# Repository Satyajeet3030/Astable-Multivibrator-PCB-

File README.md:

# Astable Multivibrator PCB Design

Overview
This project is a PCB design of an Astable Multivibrator created using KiCad.

 Features
- Two-transistor astable multivibrator
- Through-hole components
- Single-layer PCB
- Compact board layout

 Software
- KiCad 9

 Files Included
- Schematic
- PCB Layout
- Gerber Files
- Drill Files

 Author
Satyajeet Salokhe

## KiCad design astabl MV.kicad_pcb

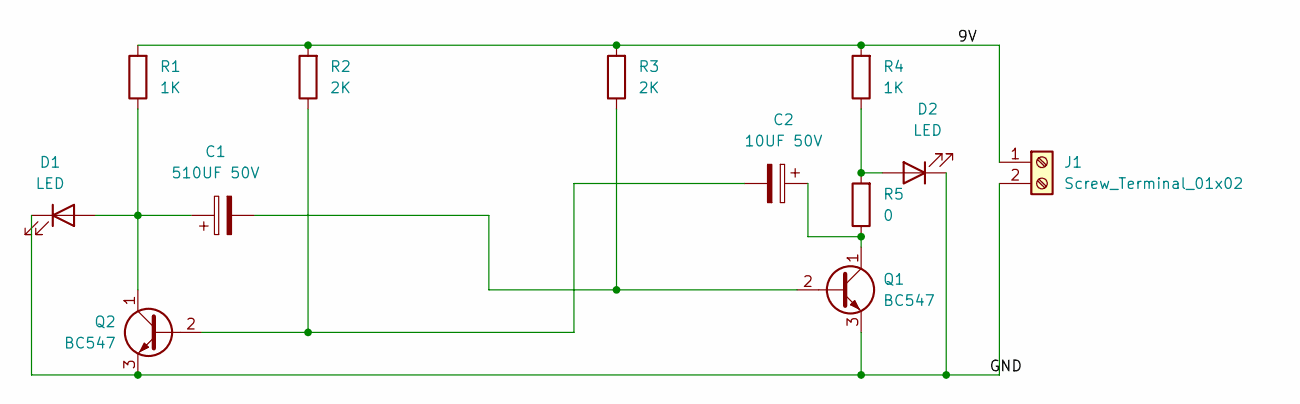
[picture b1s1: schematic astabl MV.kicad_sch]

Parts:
C1: 510UF 50V; CP_Radial_D5.0mm_P2.50mm
C2: 10UF 50V; CP_Radial_D5.0mm_P2.50mm
D1, D2: LED; LED_D5.0mm
J1: Screw_Terminal_01x02; TerminalBlock_MaiXu_MX126-5.0-02P_1x02_P5.00mm
Q1, Q2: BC547; TO-92_Inline
R1, R4: 1K; R_Axial_DIN0204_L3.6mm_D1.6mm_P7.62mm_Horizontal
R2, R3: 2K; R_Axial_DIN0204_L3.6mm_D1.6mm_P7.62mm_Horizontal
R5: 0; R_Axial_DIN0204_L3.6mm_D1.6mm_P7.62mm_Horizontal

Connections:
/9V: J1.1, R1.2, R2.2, R3.2, R4.2
/GND: D1.1 (K), D2.1 (K), J1.2, Q1.3 (E), Q2.3 (E)
unnamed: C1.1, D1.2 (A), Q2.1 (C), R1.1
unnamed: D2.2 (A), R4.1, R5.2
unnamed: C1.2, Q1.2 (B), R3.1
unnamed: C2.1, Q1.1 (C), R5.1
unnamed: C2.2, Q2.2 (B), R2.1

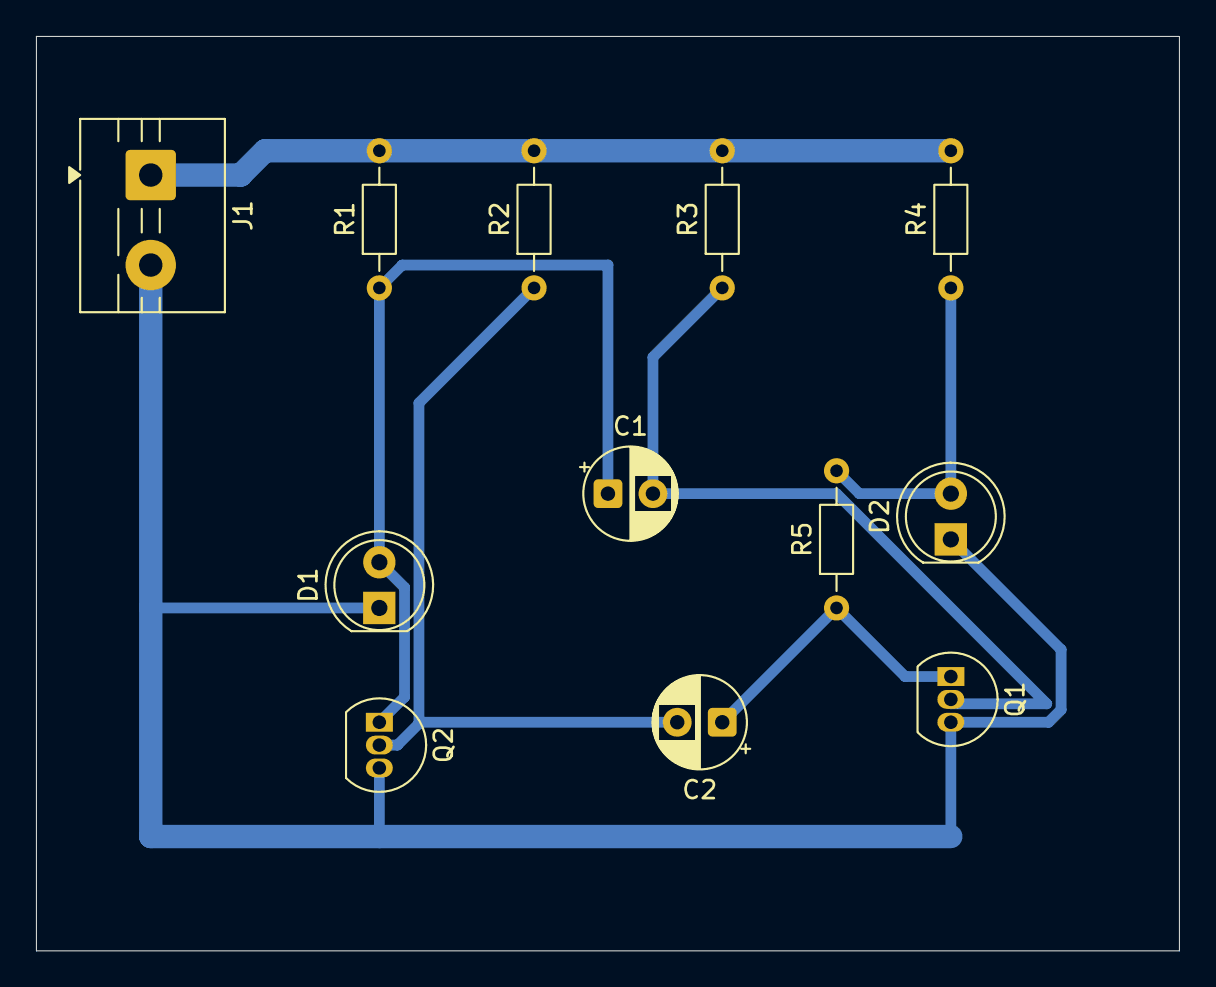
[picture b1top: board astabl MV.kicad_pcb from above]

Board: 2 copper layers, 63.5 x 50.8 mm, 12 parts (0 on the bottom side), 7 nets.
